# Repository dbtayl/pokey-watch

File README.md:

pokey-watch
===========
A project to make an ARM-based chromatic tuner for musical instruments.

It uses the KISS FFT library (http://kissfft.sourceforge.net/) to
analyze the frequencies present, then maps to a pitch and determines
whether the tone played is in-tune.

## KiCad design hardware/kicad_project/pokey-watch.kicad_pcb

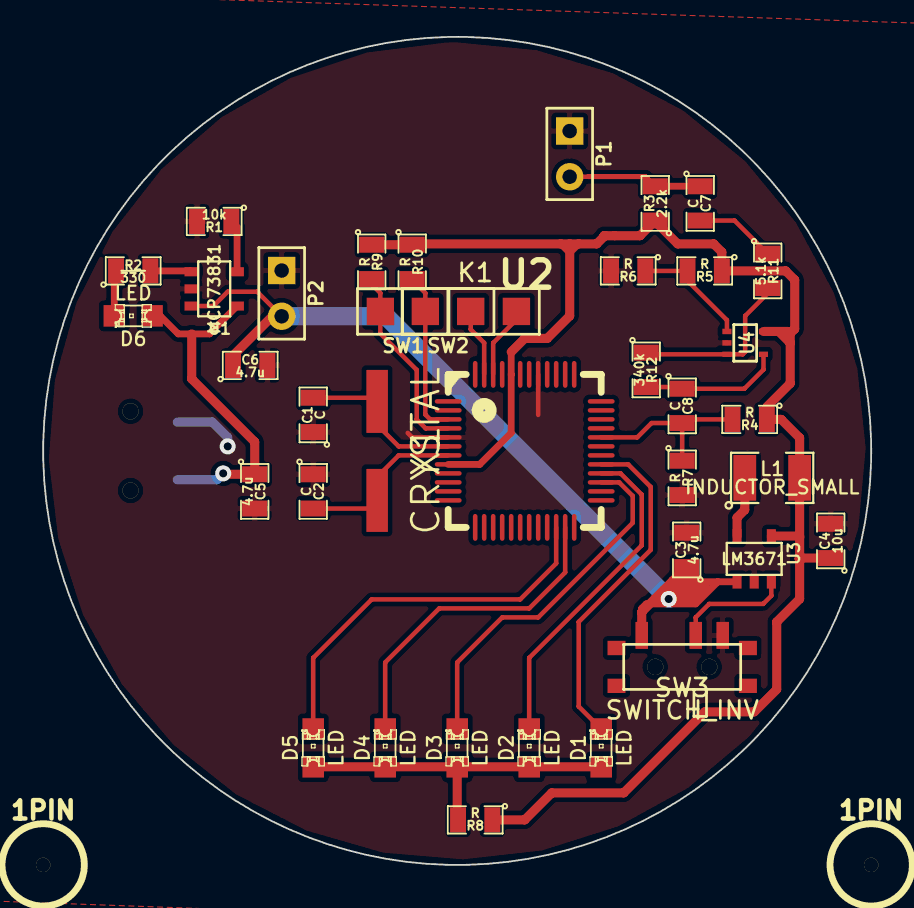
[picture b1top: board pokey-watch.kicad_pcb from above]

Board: 2 copper layers, 46.0 x 46.0 mm, 41 parts (1 on the bottom side), 27 nets.

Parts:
1PIN, 1PIN#2: P***; 1pin
C1, C2, C7, C8: C; SM0805
C3, C5, C6: 4.7u; SM0805
C4: 10u; SM0805
CON1: USB-MINI-B; USB_MINI_B
D1, D2, D3, D4, D5, D6: LED; LED-0805
K1: CONN_3; PIN_ARRAY_3X1
L1: INDUCTOR_SMALL; SM1210
P1, P2: CONN_2; PIN_ARRAY_2X1
R1: 10k; SM0805
R2: ~330; SM0805
R3: 2.2k; SM0805
R4, R5, R6, R7, R8, R9, R10: R; SM0805
R11: 5.1k; SM0805
R12: 340k; SM0805
SW1, SW2: SW_PUSH_SMALL; PIN_ARRAY_2X1
SW3: SWITCH_INV; SW_cus-12tb
U1: MCP73831; SOT23-5
U2: LPC1313_LQFP48; LQFT48_TQFP48_Reflow_RefA_06Oct2013
U3: LM3671; SOT23-5
U4: FAN4931; SOT353
X1: CRYSTAL; crystal_csm3x

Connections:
3V3: C4.1, L1.2, R3.1, R4.1, R5.1, R8.1, R9.1, R10.1, U2.8, U2.44, U3.4, U4.5
AMP_OUT: C8.2, R4.2, R7.1, U2.32
GND: C1.1, C2.1, C3.2, C4.2, C5.2, C6.2, CON1.5, P1.1, P2.1, R1.2, R6.2, R7.2, SW3.3, U1.2, U2.5, U2.41, U3.2, U4.2
LED_CENTER: D3.2, U2.27
LED_FLAT: D4.2, U2.23
LED_SHARP: D2.2, U2.28
LED_VFLAT: D5.2, U2.22
LED_VSHARP: D1.2, U2.29
MIC_OUT: C7.2, R11.1
unnamed: R1.1, U1.5
unnamed: L1.1, U3.5
unnamed: R2.2, U1.1
unnamed: D6.2, R2.1
unnamed: C7.1, P1.2, R3.2
unnamed: R11.2, R12.1, U4.3
unnamed: R5.2, R6.1, U4.1
unnamed: C8.1, R12.2, U4.4
unnamed: D1.1, D2.1, D3.1, D4.1, D5.1, R8.2
unnamed: C1.2, U2.6, X1.2
unnamed: C2.2, U2.7, X1.1
PGRM: R9.2, SW1.2, U2.4
REG_EN: SW3.2, U3.3
RESET: R10.2, SW2.2, U2.3
RX: K1.3, U2.46
TX: K1.2, U2.47
VBAT: C3.1, C6.1, P2.2, SW3.1, U1.3, U3.1
VUSB: C5.1, CON1.1, D6.1, U1.4

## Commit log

2014-08-07 Initial commit of source files; should be fully-functional, if a little primitive.
2014-08-07 Added KiCad hardware design files (schematic and layout)
2014-08-07 Moved hardware directory around to allow for gcode to be added down the road
2014-08-11 Forgot to copy main.c into this project... oops.
2014-08-11 Also forgot pitches file... That might be kind of important
2014-08-12 Some averaging added to try to make readings more reliable. Same code as used in YouTube alpha-testing video.
2014-08-23 Moved pitch detection algorithm into its own file to allow for easy switching between different algorithms (FFT- and autocorrelation-based, for now)
2014-08-24 Updated schematic with real net names for the program and reset pins; changed picth-detection algorithm to average 5 points of the FFT for improved accuracy.
2014-12-08 Added note to look up Goertzel algorithm
2015-01-19 Added gcode
2015-01-19 Fixed a few small gcode errors. Upped feed rates. Removed some unnecessary passes to speed up milling.
2015-01-20 Fixed gcode: Added gcode messages to help prevent PEBKAC. Fixed an issue with the lid where the final cut would plunge too deep initially. Rounded male portion of hinge to make it fit better. Expande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
2015-01-22 More gcode fixes- this was used in the final version with minimal manual rework after. Mostly patch up smoothing errors and added proper rounding of the male hinge corners. Also adds code to cut out 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
2015-01-26 Improved LED handling; some debugging work
2015-01-26 Updated LED code. Cleaned up old code.
2015-01-26 More cleanups. Keep LEDs off when pitch is outside of detection range. Shift detection range up to minimize effect of sampling/FFT errors on cents reported.
2015-01-30 Use larger FFT for better accuracy; expand range of notes detected.
